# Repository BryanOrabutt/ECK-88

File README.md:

# ECK-88

This project is an attempt to recreate the Intel ECK-88 development kit using KiCAD software to recreate the board and schematics. There have been some additions to the board
to aid in both educational and demonstrational use. These new additions are outlined below:

 * Every address, data, and control signal is broken out to an IO header to allow for logic analyzer probing.
 * Every address, data, and most control signals are broken out to LEDs for use when single stepping.
 * A clock select was added that allows selection between the main 4 Mhz clock, an external clock, and a debounced push button
   for single stepping.
 * All GPIO lines are broken out to headers (rather than no connect from the original ECK-88)
 * All chips are socketed to allow replacement and reprogramming with ease.
 * DC Barrel jack and LM1084 linear regulator added to allow wide range of power inputs.

## Modification

If you wish to make any modifications to the current board, all of the files are designed in KiCAD. The KiCAD software can be obtained here: http://kicad.org/. All of the
custom symbols and footprints are found in the Libraries and Libraries.pretty folders and will need to be manually added to the KiCAD library search path. The board was
designed to meet the requirements of OSH Park's fabrication rules. For more information see: http://docs.oshpark.com/design-tools/kicad/

## License

This project is licensed under the MIT License - see the [LICENSE](LICENSE) file for details

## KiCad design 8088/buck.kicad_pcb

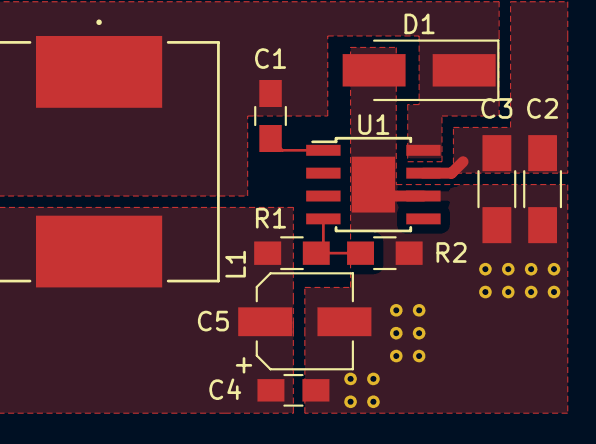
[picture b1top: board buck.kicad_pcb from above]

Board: 2 copper layers, 10 parts (0 on the bottom side), 6 nets.

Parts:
C1: 10nF; C_0805_HandSoldering
C2, C3: 4.7uF; C_1206_HandSoldering
C4: 100nF; C_0805_HandSoldering
C5: 220uF; CP_Elec_5x5.3
D1: STPS5L60U; D_SMA_Handsoldering
L1: 22uH; SRR1208-220ML
R1: 30.9K±0.1%; R_0805_HandSoldering
R2: 10K±0.1%; R_0805_HandSoldering
U1: TPS5430; TI_SO-PowerPAD-8

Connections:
+5V: C4.1, C5.1, L1.2, R1.1
+BATT: C2.1, C3.1, U1.7
/PH: C1.2, D1.1, L1.1, U1.8
GND: C2.2, C3.2, C4.2, C5.2, D1.2, R2.2, U1.6, U1.9
unnamed: C1.1, U1.1
unnamed: R1.2, R2.1, U1.4

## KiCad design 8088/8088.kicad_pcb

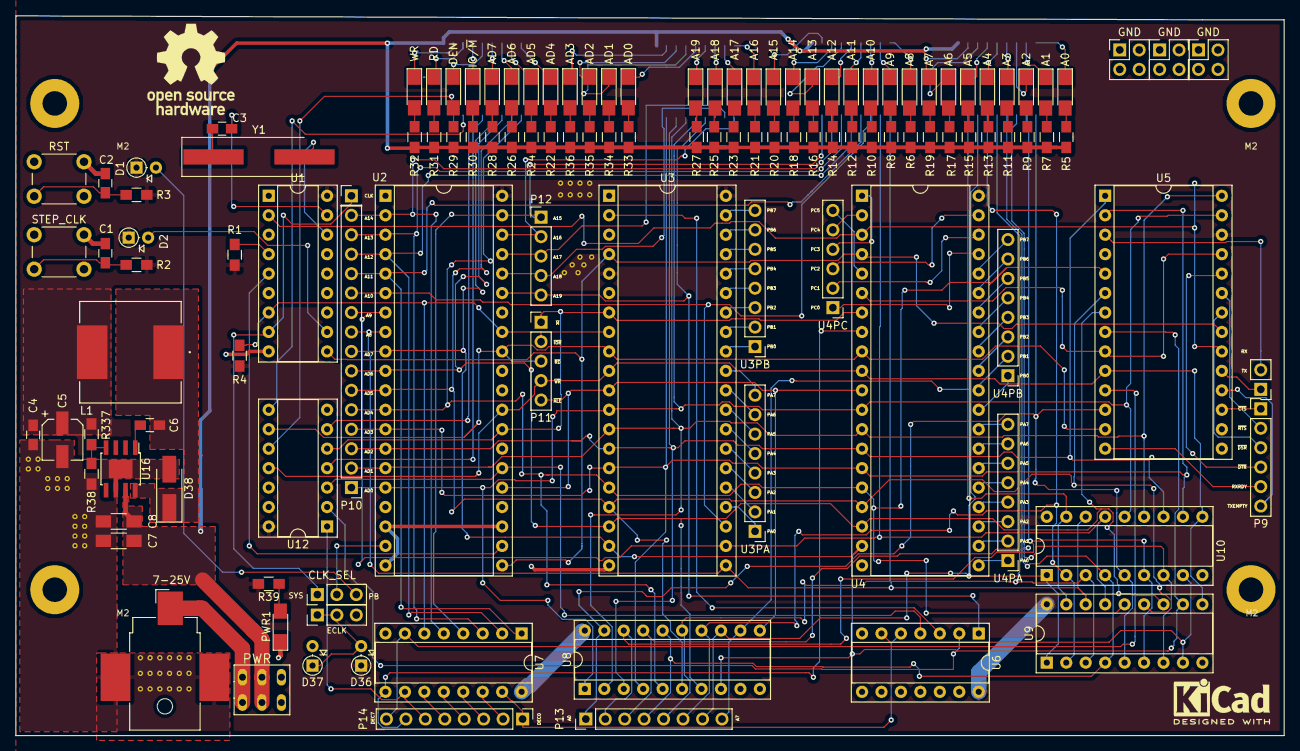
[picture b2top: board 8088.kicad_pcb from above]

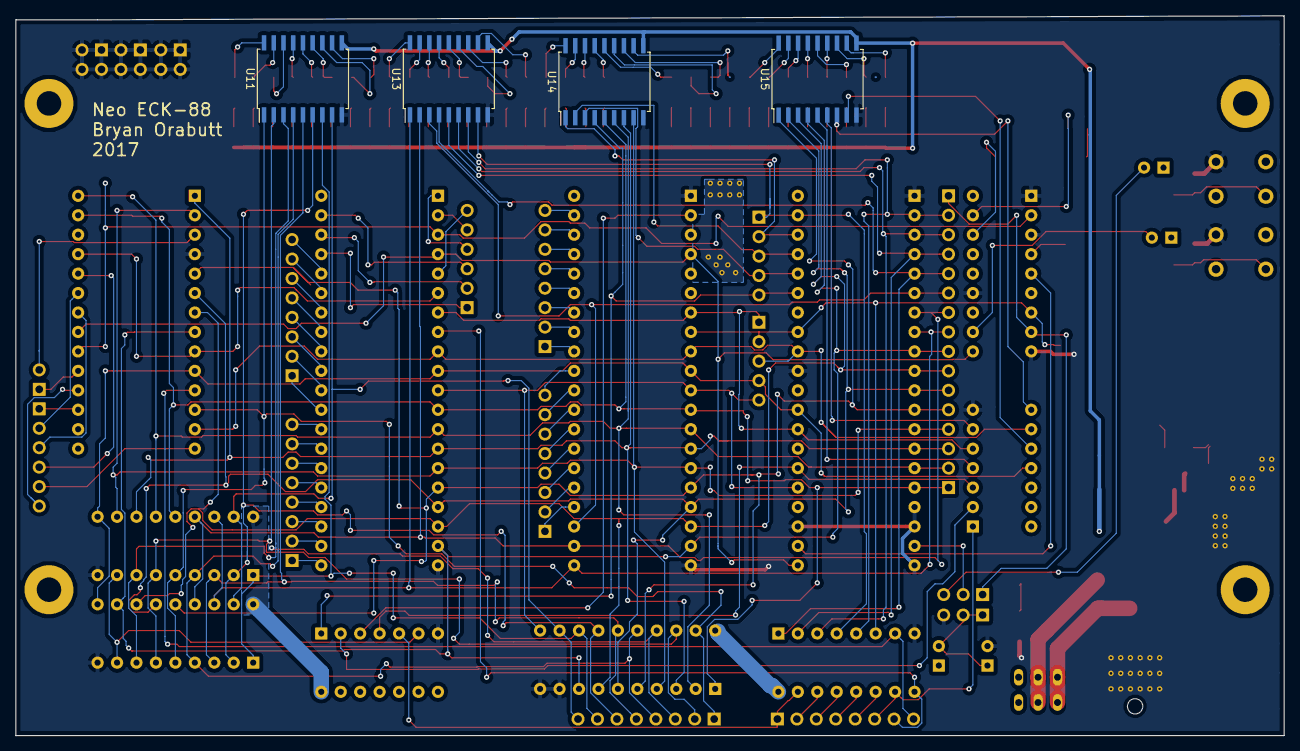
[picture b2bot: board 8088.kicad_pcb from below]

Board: 2 copper layers, 165.6 x 94.0 mm, 125 parts (4 on the bottom side), 182 nets.

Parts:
7-25V: BARREL_JACK; Barrel_Jack_CUI_PJ-036AH-SMT
A0: A0; LED_1206_HandSoldering
A1: A1; LED_1206_HandSoldering
A2: A2; LED_1206_HandSoldering
A3: A3; LED_1206_HandSoldering
A4: A4; LED_1206_HandSoldering
A5: A5; LED_1206_HandSoldering
A6: A6; LED_1206_HandSoldering
A7: A7; LED_1206_HandSoldering
A8: A8; LED_1206_HandSoldering
A9: A9; LED_1206_HandSoldering
A10: A10; LED_1206_HandSoldering
A11: A11; LED_1206_HandSoldering
A12: A12; LED_1206_HandSoldering
A13: A13; LED_1206_HandSoldering
A14: A14; LED_1206_HandSoldering
A15: A15; LED_1206_HandSoldering
A16: A16; LED_1206_HandSoldering
A17: A17; LED_1206_HandSoldering
A18: A18; LED_1206_HandSoldering
A19: A19; LED_1206_HandSoldering
AD0: AD0; LED_1206_HandSoldering
AD1: AD1; LED_1206_HandSoldering
AD2: AD2; LED_1206_HandSoldering
AD3: AD3; LED_1206_HandSoldering
AD4: AD4; LED_1206_HandSoldering
AD5: AD5; LED_1206_HandSoldering
AD6: AD6; LED_1206_HandSoldering
AD7: AD7; LED_1206_HandSoldering
C1, C2: 1uF; C_0805_HandSoldering
C3: 5pF; C_0805_HandSoldering
C4: 100nF; C_0805_HandSoldering
C5: 220uF; CP_Elec_5x5.3
C6: 10nF; C_0805_HandSoldering
C7, C8: 4.7uF; C_1206_HandSoldering
CLK: Pin_Header_Straight_1x01_Pitch2.54mm
CLK_SEL: CLK_SEL; Pin_Header_Straight_1x03_Pitch2.54mm
D1, D2, D36, D37: 1N914; D_DO-35_SOD27_P2.54mm_Vertical_AnodeUp
D38: STPS5L60U; D_SMA_Handsoldering
DEN: DEN; LED_1206_HandSoldering
GND: GND; Pin_Header_Straight_2x02_Pitch2.54mm
GND#2, GND#3: GND; Pin_Header_Straight_2x02_Pitch2.54mm
IO/~M: IO/~M; LED_1206_HandSoldering
JP2: JUMPER3; Pin_Header_Straight_1x03_Pitch2.54mm
L1: 22uH; SRR1208-220ML
P9: CONN_01X06; Pin_Header_Straight_1x06_Pitch2.54mm
P10: CONN_01X15; Pin_Header_Straight_1x15_Pitch2.54mm
P11, P12: CONN_01X05; Pin_Header_Straight_1x05_Pitch2.54mm
P13, P14: CONN_01X08; Pin_Header_Straight_1x08_Pitch2.54mm
PWR: PWR; SPST-SLIDE
PWR1: PWR; LED_1206_HandSoldering
R1, R2, R3, R4, R39: 7.5K; R_0805_HandSoldering
R5, R6, R7, R8, R9, R10, R11, R12, R13, R14, R15, R16, R17, R18, R19, R20, R21, R22, R23, R24, R25, R26, R27, R28, R29, R30, R31, R32, R33, R34, R35, R36: 1K; R_0805_HandSoldering
R38: 10K±0.1%; R_0805_HandSoldering
R337: 30.9K±0.1%; R_0805_HandSoldering
RD: RD; LED_1206_HandSoldering
RST: RESET; SW_PUSH_6mm_h5mm
RX/TX: RX/TX; Pin_Header_Straight_1x02_Pitch2.54mm
STEP_CLK: STEP_CLK; SW_PUSH_6mm_h5mm
U1: 8284; DIP-18_W7.62mm_Socket
U2: 8088; DIP-40_W15.24mm_Socket
U3: 8755A; DIP-40_W15.24mm_Socket
U3PA: U3PA; Pin_Header_Straight_1x08_Pitch2.54mm
U3PB: U3PB; Pin_Header_Straight_1x08_Pitch2.54mm
U4: 8155; DIP-40_W15.24mm_Socket
U4PA: U4PA; Pin_Header_Straight_1x08_Pitch2.54mm
U4PB: U4PB; Pin_Header_Straight_1x08_Pitch2.54mm
U4PC: U4PC; Pin_Header_Straight_1x06_Pitch2.54mm
U5: 8251A; DIP-28_W15.24mm_Socket
U6: 74LS32; DIP-14_W7.62mm_Socket
U7: 74LS138; DIP-16_W7.62mm_Socket
U8: 8282; DIP-20_W7.62mm_Socket
U9, U10: 2114; DIP-18_W7.62mm_Socket
U11, U13, U14, U15: ULN2803ADWR; SOIC-18W_7.5x11.6mm_Pitch1.27mm
U12: 74LS14; DIP-14_W7.62mm_Socket
U16: TPS5430; TI_SO-PowerPAD-8
WR: WR; LED_1206_HandSoldering
Y1: 12MHz; Crystal_SMD_HC49-SD_HandSoldering

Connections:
+5V: C4.1, C5.1, D1.1, D2.1, D36.1, L1.2, R1.1, R2.2, R3.2, R4.2, R39.2, R337.1, U1.18, U2.40, U3.5, U3.40, U4.40, U5.26, U6.14, U7.16, U8.20, U9.18, U10.18, U12.14
+12V: 7-25V.1, PWR.1, PWR.6
/3PA0: U3.24, U3PA.1
/3PA1: U3.25, U3PA.2
/3PA2: U3.26, U3PA.3
/3PA3: U3.27, U3PA.4
/3PA4: U3.28, U3PA.5
/3PA5: U3.29, U3PA.6
/3PA6: U3.30, U3PA.7
/3PA7: U3.31, U3PA.8
/3PB0: U3.32, U3PB.1
/3PB1: U3.33, U3PB.2
/3PB2: U3.34, U3PB.3
/3PB3: U3.35, U3PB.4
/3PB4: U3.36, U3PB.5
/3PB5: U3.37, U3PB.6
/3PB6: U3.38, U3PB.7
/3PB7: U3.39, U3PB.8
/4PA0: U4.21, U4PA.1
/4PA1: U4.22, U4PA.2
/4PA2: U4.23, U4PA.3
/4PA3: U4.24, U4PA.4
/4PA4: U4.25, U4PA.5
/4PA5: U4.26, U4PA.6
/4PA6: U4.27, U4PA.7
/4PA7: U4.28, U4PA.8
/4PB0: U4.29, U4PB.1
/4PB1: U4.30, U4PB.2
/4PB2: U4.31, U4PB.3
/4PB3: U4.32, U4PB.4
/4PB4: U4.33, U4PB.5
/4PB5: U4.34, U4PB.6
/4PB6: U4.35, U4PB.7
/4PB7: U4.36, U4PB.8
/4PC0: U4.37, U4PC.1
/4PC1: U4.38, U4PC.2
/4PC2: U4.39, U4PC.3
/4PC3: U4.1, U4PC.4
/4PC4: U4.2, U4PC.5
/4PC5: U4.5, U4PC.6
/A0: P13.1, U5.12, U8.19, U9.5, U10.5, U11.1
/A1: P13.2, U8.18, U9.6, U10.6, U11.2
/A2: P13.3, U8.17, U9.7, U10.7, U11.3
/A3: P13.4, U8.16, U9.4, U10.4, U11.4
/A4: P13.5, U8.15, U9.3, U10.3, U11.5
/A5: P13.6, U8.14, U9.2, U10.2, U11.6
/A6: P13.7, U8.13, U9.1, U10.1, U11.7
/A7: P13.8, U8.12, U9.17, U10.17, U11.8
/A8: P10.9, U2.8, U3.21, U9.16, U10.16, U13.1
/A9: P10.10, U2.7, U3.22, U9.15, U10.15, U13.2
/A10: P10.11, U2.6, U3.23, U13.3
/A11: P10.12, U2.5, U7.1, U13.4
/A12: P10.13, U2.4, U7.2, U13.5
/A13: P10.14, U2.3, U7.3, U13.6
/A14: P10.15, U2.2, U7.5, U13.7
/A15: P12.1, U2.39, U7.4, U13.8
/A16: P12.2, U2.38, U14.1
/A17: P12.3, U2.37, U14.2
/A18: P12.4, U2.36, U14.3
/A19: P12.5, U2.35, U6.1, U14.4
/AD0: P10.1, U2.16, U3.12, U4.12, U5.27, U8.1, U10.14, U14.5
/AD1: P10.2, U2.15, U3.13, U4.13, U5.28, U8.2, U10.13, U14.6
/AD2: P10.3, U2.14, U3.14, U4.14, U5.1, U8.3, U10.12, U14.7
/AD3: P10.4, U2.13, U3.15, U4.15, U5.2, U8.4, U10.11, U14.8
/AD4: P10.5, U2.12, U3.16, U4.16, U5.5, U8.5, U9.14, U15.1
/AD5: P10.6, U2.11, U3.17, U4.17, U5.6, U8.6, U9.13, U15.2
/AD6: P10.7, U2.10, U3.18, U4.18, U5.7, U8.7, U9.12, U15.3
/AD7: P10.8, U2.9, U3.19, U4.19, U5.8, U8.8, U9.11, U15.4
/ALE: P11.5, U2.25, U3.11, U4.11, U8.11
/Buck Converter/PH: C6.2, D38.1, L1.1, U16.8
/DEC0: P14.1, U6.5, U7.15
/DEC1: P14.2, U7.14
/DEC2: P14.3, U7.13
/DEC3: P14.4, U7.12
/DEC4: P14.5, U7.11
/DEC5: P14.6, U7.10, U12.1
/DEC6: P14.7, U4.8, U7.9
/DEC7: P14.8, U5.11, U7.7
/ECLK: D36.2, D37.1, JP2.1, JP2.2
/IO/~M: P11.1, U2.28, U3.7, U4.7, U12.5
/RXRDY: P9.5, U5.14
/TXEMP: P9.6, U5.18
/~CTS: P9.1, U5.17
/~DEN: U2.26, U6.4, U12.3
/~DSR: P9.3, U5.22
/~DTR: P9.4, U5.24
/~IOR: P11.2, R4.1, U1.7, U2.33, U3.8, U7.6
/~RD: P11.3, U2.32, U3.9, U4.9, U5.13, U12.9
/~RTS: P9.2, U5.23
/~WR: P11.4, U2.29, U3.10, U4.10, U5.10, U9.10, U10.10, U12.11
GND: 7-25V.2, 7-25V.3, C1.2, C2.2, C4.2, C5.2, C7.2, C8.2, D37.2, D38.2, GND.1, GND.2, GND.3, GND.4, GND#2.1, GND#2.2, GND#2.3, GND#2.4, GND#3.1, GND#3.2, GND#3.3, GND#3.4, JP2.3, PWR1.1, R38.2, RST.1, STEP_CLK.1, U1.1, U1.3, U1.9, U1.13, U2.1, U2.17, U2.18, U2.20, U2.23, U2.31, U3.1, U3.20, U4.20, U5.4, U6.7, U7.8, U8.9, U8.10, U9.9, U10.9, U11.9, U12.7, U13.9, U14.9, U15.9, U16.6, U16.9
unnamed: C1.1, R2.1, STEP_CLK.2
unnamed: C2.1, R3.1, RST.2
unnamed: C3.1, U1.17
unnamed: C3.2, Y1.1
unnamed: C6.1, U16.1
unnamed: CLK_SEL.3, D1.2
unnamed: D2.2, U1.11
unnamed: A0.1, U11.18
unnamed: A0.2, R5.2
unnamed: A8.1, U13.18
unnamed: A8.2, R6.2
unnamed: A1.1, U11.17
unnamed: A1.2, R7.2
unnamed: A9.1, U13.17
unnamed: A9.2, R8.2
unnamed: A2.1, U11.16
unnamed: A2.2, R9.2
unnamed: A10.1, U13.16
unnamed: A10.2, R10.2
unnamed: A3.1, U11.15
unnamed: A3.2, R11.2
unnamed: A11.1, U13.15
unnamed: A11.2, R12.2
unnamed: A4.1, U11.14
unnamed: A4.2, R13.2
unnamed: A12.1, U13.14
unnamed: A12.2, R14.2
unnamed: A5.1, U11.13
unnamed: A5.2, R15.2
unnamed: A13.1, U13.13
unnamed: A13.2, R16.2
unnamed: A6.1, U11.12
unnamed: A6.2, R17.2
unnamed: A14.1, U13.12
unnamed: A14.2, R18.2
unnamed: A7.1, U11.11
unnamed: A7.2, R19.2
unnamed: A15.1, U13.11
unnamed: A15.2, R20.2
unnamed: A16.1, U14.18
unnamed: A16.2, R21.2
unnamed: AD4.1, U15.18
unnamed: AD4.2, R22.2
unnamed: A17.1, U14.17
unnamed: A17.2, R23.2
unnamed: AD5.1, U15.17
unnamed: AD5.2, R24.2
unnamed: A18.1, U14.16
unnamed: A18.2, R25.2
unnamed: AD6.1, U15.16
unnamed: AD6.2, R26.2
unnamed: A19.1, U14.15
unnamed: A19.2, R27.2
unnamed: AD7.1, U15.15
unnamed: AD7.2, R28.2
unnamed: DEN.1, U15.14
unnamed: DEN.2, R29.2
unnamed: IO/~M.1, U15.13
unnamed: IO/~M.2, R30.2
unnamed: RD.1, U15.12
unnamed: R31.2, RD.2
unnamed: U15.11, WR.1
unnamed: R32.2, WR.2
unnamed: AD0.1, U14.14
unnamed: AD0.2, R33.2
unnamed: AD1.1, U14.13
unnamed: AD1.2, R34.2
unnamed: AD2.1, U14.12
unnamed: AD2.2, R35.2
unnamed: AD3.1, U14.11
unnamed: AD3.2, R36.2
unnamed: CLK.1, CLK_SEL.1, U1.8
unnamed: CLK_SEL.2, U2.19
unnamed: RX/TX.1, U5.19
unnamed: RX/TX.2, U5.3
unnamed: PWR1.2, R39.1
unnamed: R1.2, U1.4
unnamed: R38.1, R337.2, U16.4
unnamed: U1.2, U4.3, U5.20
unnamed: U1.5, U2.22
unnamed: U1.10, U2.21, U3.4, U4.4, U5.21
unnamed: U1.16, Y1.2
unnamed: U3.2, U6.3
unnamed: U4.6, U5.9, U5.25
unnamed: U6.6, U9.8, U10.8
unnamed: U6.2, U12.2
unnamed: U12.4, U15.5
unnamed: U12.6, U15.6
unnamed: U12.8, U15.7
unnamed: U12.10, U15.8
P_IN: C7.1, C8.1, PWR.2, PWR.5, R5.1, R6.1, R7.1, R8.1, R9.1, R10.1, R11.1, R12.1, R13.1, R14.1, R15.1, R16.1, R17.1, R18.1, R19.1, R20.1, R21.1, R22.1, R23.1, R24.1, R25.1, R26.1, R27.1, R28.1, R29.1, R30.1, R31.1, R32.1, R33.1, R34.1, R35.1, R36.1, U11.10, U13.10, U14.10, U15.10, U16.7

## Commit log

2017-09-22 Added readme
2017-09-22 Create LICENSE
2017-09-24 Fixed schematic errors and added custom component footprints for the switches/PBs
2017-09-24 Started PCB
2017-09-26 Initial PCB design finished
2017-09-26 forgot to add PCB file, oops!
2017-09-26 Added PCB images
2017-09-27 Fixed pin number discrepency
2017-09-27 Fixed schematic error
2017-09-27 Fixed pin 26 discrepency on PCB layout
2017-09-27 Fixed PCB routing issue
2017-09-30 Adding IO headers to schematic
2017-09-30 Removed unused libraries
2017-09-30 Updated libraries. Added IO headers to schematics. TODO: Route ISA bus
2017-10-01 Second board revision down. Added bling :)
2017-10-01 Fixed typo
2017-10-01 Updated liscense.
2017-10-01 Formatting.
2017-10-01 Removed redundant files
2017-10-01 Added gerbers.
2017-10-01 Forgot to add footprint library that was used
2017-10-10 Fixed chip socket widths
2017-10-10 Reformatted README
2017-10-13 Changed regulator
2017-10-13 Updated board layout
2017-10-13 Fixed symbol issue
2017-10-13 Generated gerbers.
2017-10-19 Updated PCB to use top side power plane
2017-10-19 Added ULN2803 symbol
2017-10-19 Fixed some track routing
2017-10-21 Board revised based on prototype
2017-10-21 Fixed some silkscreen issues
2017-10-23 Fixed issue with ECLK
2017-10-27 Started FPGA programmer for 8755A
2017-10-27 fixed logic issue with programmer.
2017-10-29 Renamed files
2017-10-29 Updated gitignore
2017-10-29 Moved source files around
2017-10-29 Removed ignored files
2017-10-30 Generated binaries
2017-10-30 Fixed state logic
2017-10-30 Added python hexwriter program to write instructions to ROM
2017-12-01 Board rev2 done. Added buck converter circuit
2017-12-06 Updated programmer logic
2021-11-09 Update README.md
    https://forum.kicad.info/t/warning-avoid-all-links-to-kicad-pcb-org-use-kicad-org/31521

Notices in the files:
parts and their libraries:
Copyright 2016 Accelerated Designs. All rights reserved.
